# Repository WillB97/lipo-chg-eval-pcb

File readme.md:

# BQ25792/MP2759 LiPo Charger Evaluation Board

[GitHub Pages site](https://willb97.github.io/lipo-chg-eval-pcb/Browse/charger-compare-navigate.html).

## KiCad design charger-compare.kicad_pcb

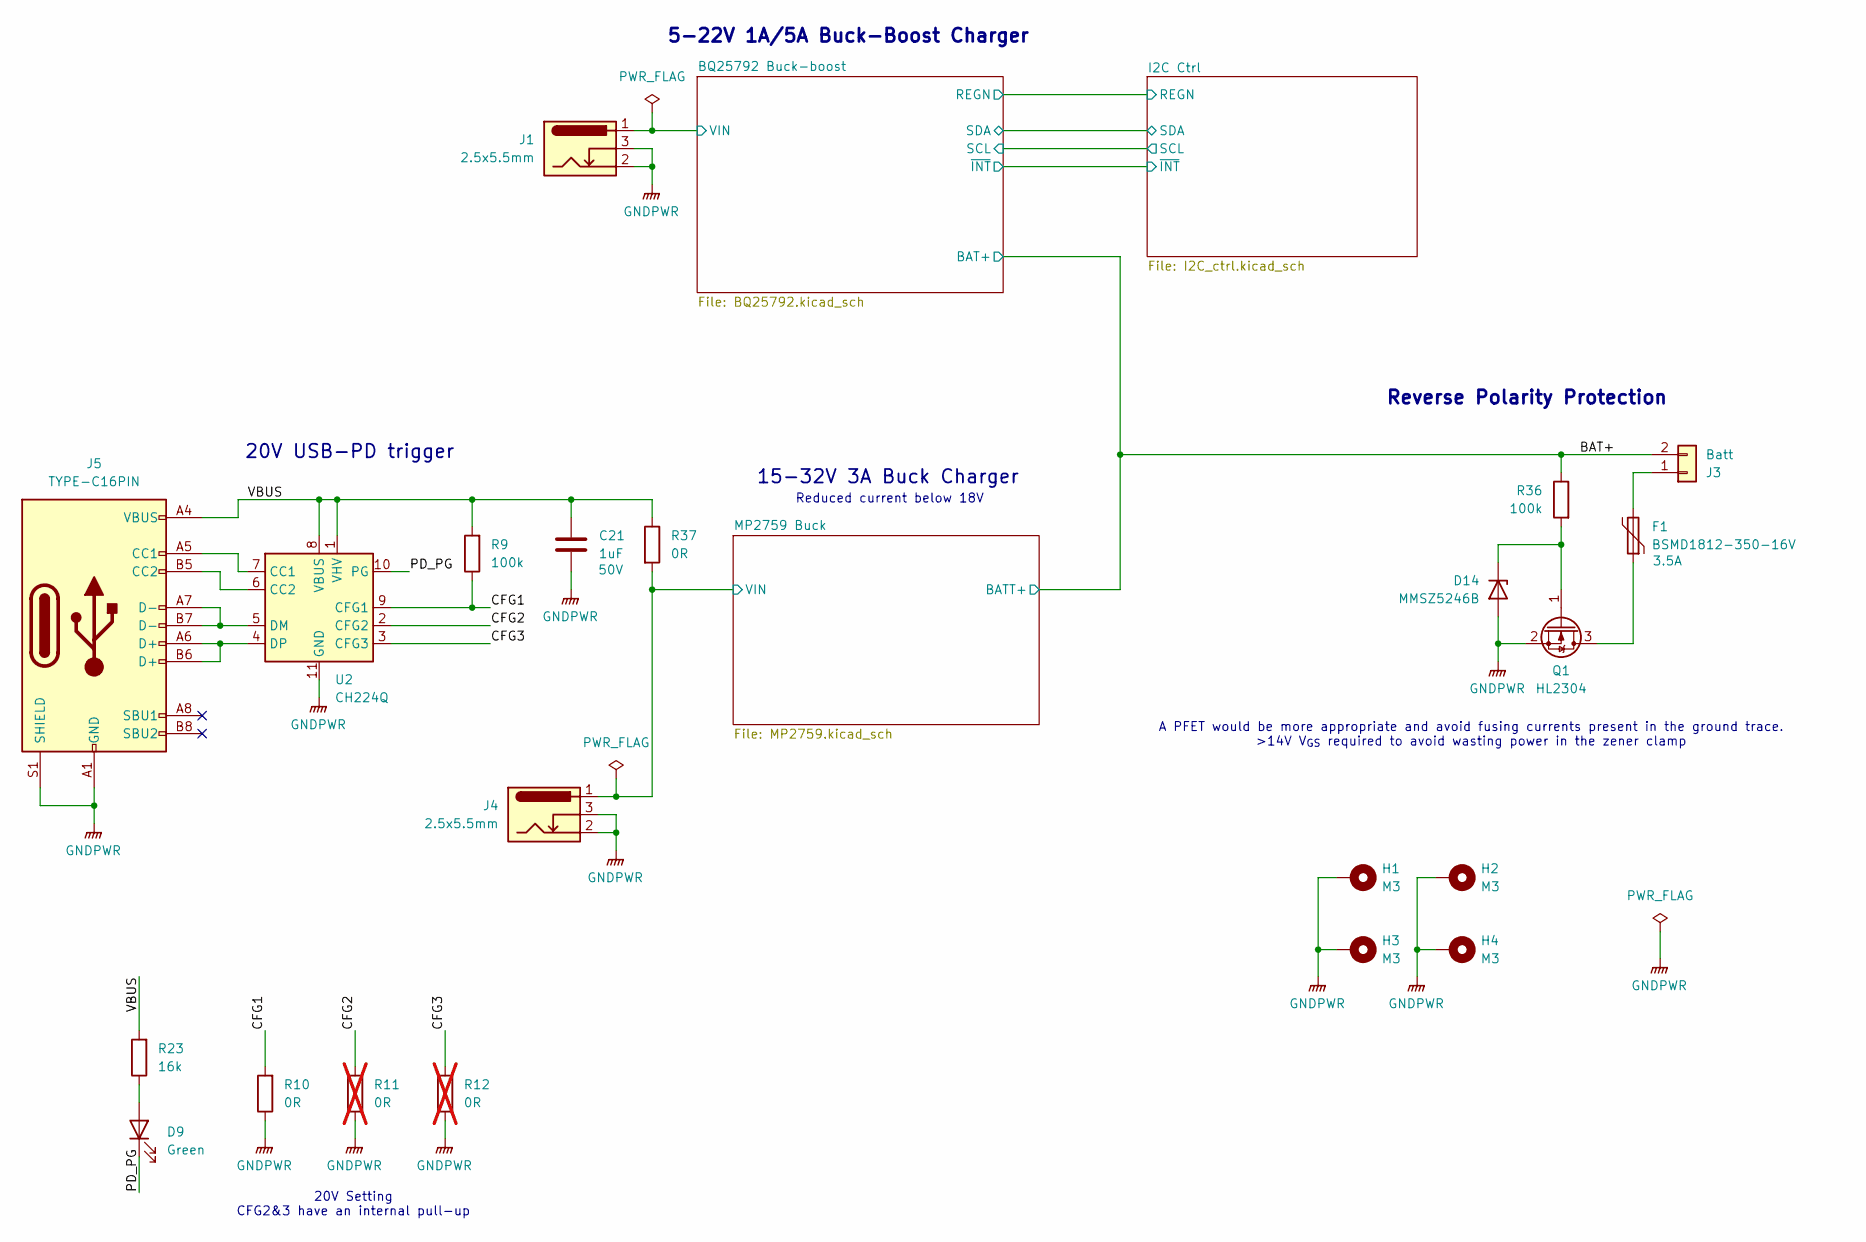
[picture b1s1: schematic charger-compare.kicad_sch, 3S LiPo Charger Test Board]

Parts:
C21: 1uF; C_0603_1608Metric; Voltage 50V; JLC C15849
D9: Green; LED_0805_2012Metric; JLC C2297
D14: MMSZ5246B; D_SOD-123; LCSC C19077429
F1: BSMD1812-350-16V; Fuse_1812_4532Metric_Pad1.30x3.40mm_HandSolder; Rating 3.5A; LCSC C5301865
H1, H2, H3, H4: M3; MountingHole_3.2mm_M3_Pad
J1, J4: 2.5x5.5mm; DC005-2.5; LCSC C7507454
J3: Batt; AMASS_XT60-M_1x02_P7.20mm_Vertical
J5: TYPE-C16PIN; USB_C_Receptacle_Palconn_UTC16-G; LCSC C393939
Q1: HL2304; SOT-23; LCSC C7420346
R9, R36: 100k; R_0402_1005Metric
R10: 0R; R_0603_1608Metric
R11, R12: 0R; R_0603_1608Metric; not fitted
R23: 16k; R_0402_1005Metric
R37: 0R; R_1206_3216Metric
U2: CH224Q; DFN-10_2x2mm_P0.4mm; LCSC C46061833

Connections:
/BAT+: J3.2, R36.1; also elsewhere on the board
/CFG1: R9.1, R10.2, U2.9 (CFG1)
/CFG2: R11.2, U2.2 (CFG2)
/CFG3: R12.2, U2.3 (CFG3)
/MP2759 Buck/VIN: J4.1, R37.2; also elsewhere on the board
/PD_PG: D9.1 (K), U2.10 (PG)
/VBUS: C21.1, J5.A4 (VBUS), J5.A9 (VBUS), J5.B4 (VBUS), J5.B9 (VBUS), R9.2, R23.2, R37.1, U2.1 (VHV), U2.8 (VBUS)
GNDPWR: C21.2, D14.2 (A), H1.1, H2.1, H3.1, H4.1, J1.2, J1.3, J4.2, J4.3, J5.A1 (GND), J5.A12 (GND), J5.B1 (GND), J5.B12 (GND), J5.S1 (SHIELD), Q1.2 (S), R10.1, R11.1, R12.1, U2.11 (GND); also elsewhere on the board
unnamed: D9.2 (A), R23.1
unnamed: D14.1 (K), Q1.1 (G), R36.2
unnamed: F1.2, J3.1
unnamed: J5.A5 (CC1), U2.7 (CC1)
unnamed: J5.B5 (CC2), U2.6 (CC2)
unnamed: F1.1, Q1.3 (D)
unnamed: J5.A7 (D-), J5.B7 (D-), U2.5 (DM)
unnamed: J5.A6 (D+), J5.B6 (D+), U2.4 (DP)
VBUS: J1.1; also elsewhere on the board

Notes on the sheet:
20V USB-PD trigger
Reverse Polarity Protection
5-22V 1A/5A Buck-Boost Charger
A PFET would be more appropriate and avoid fusing currents present in the ground trace. >14V V_{GS} required to avoid wasting power in the zener clamp
20V Setting CFG2&3 have an internal pull-up
Reduced current below 18V
15-32V 3A Buck Charger

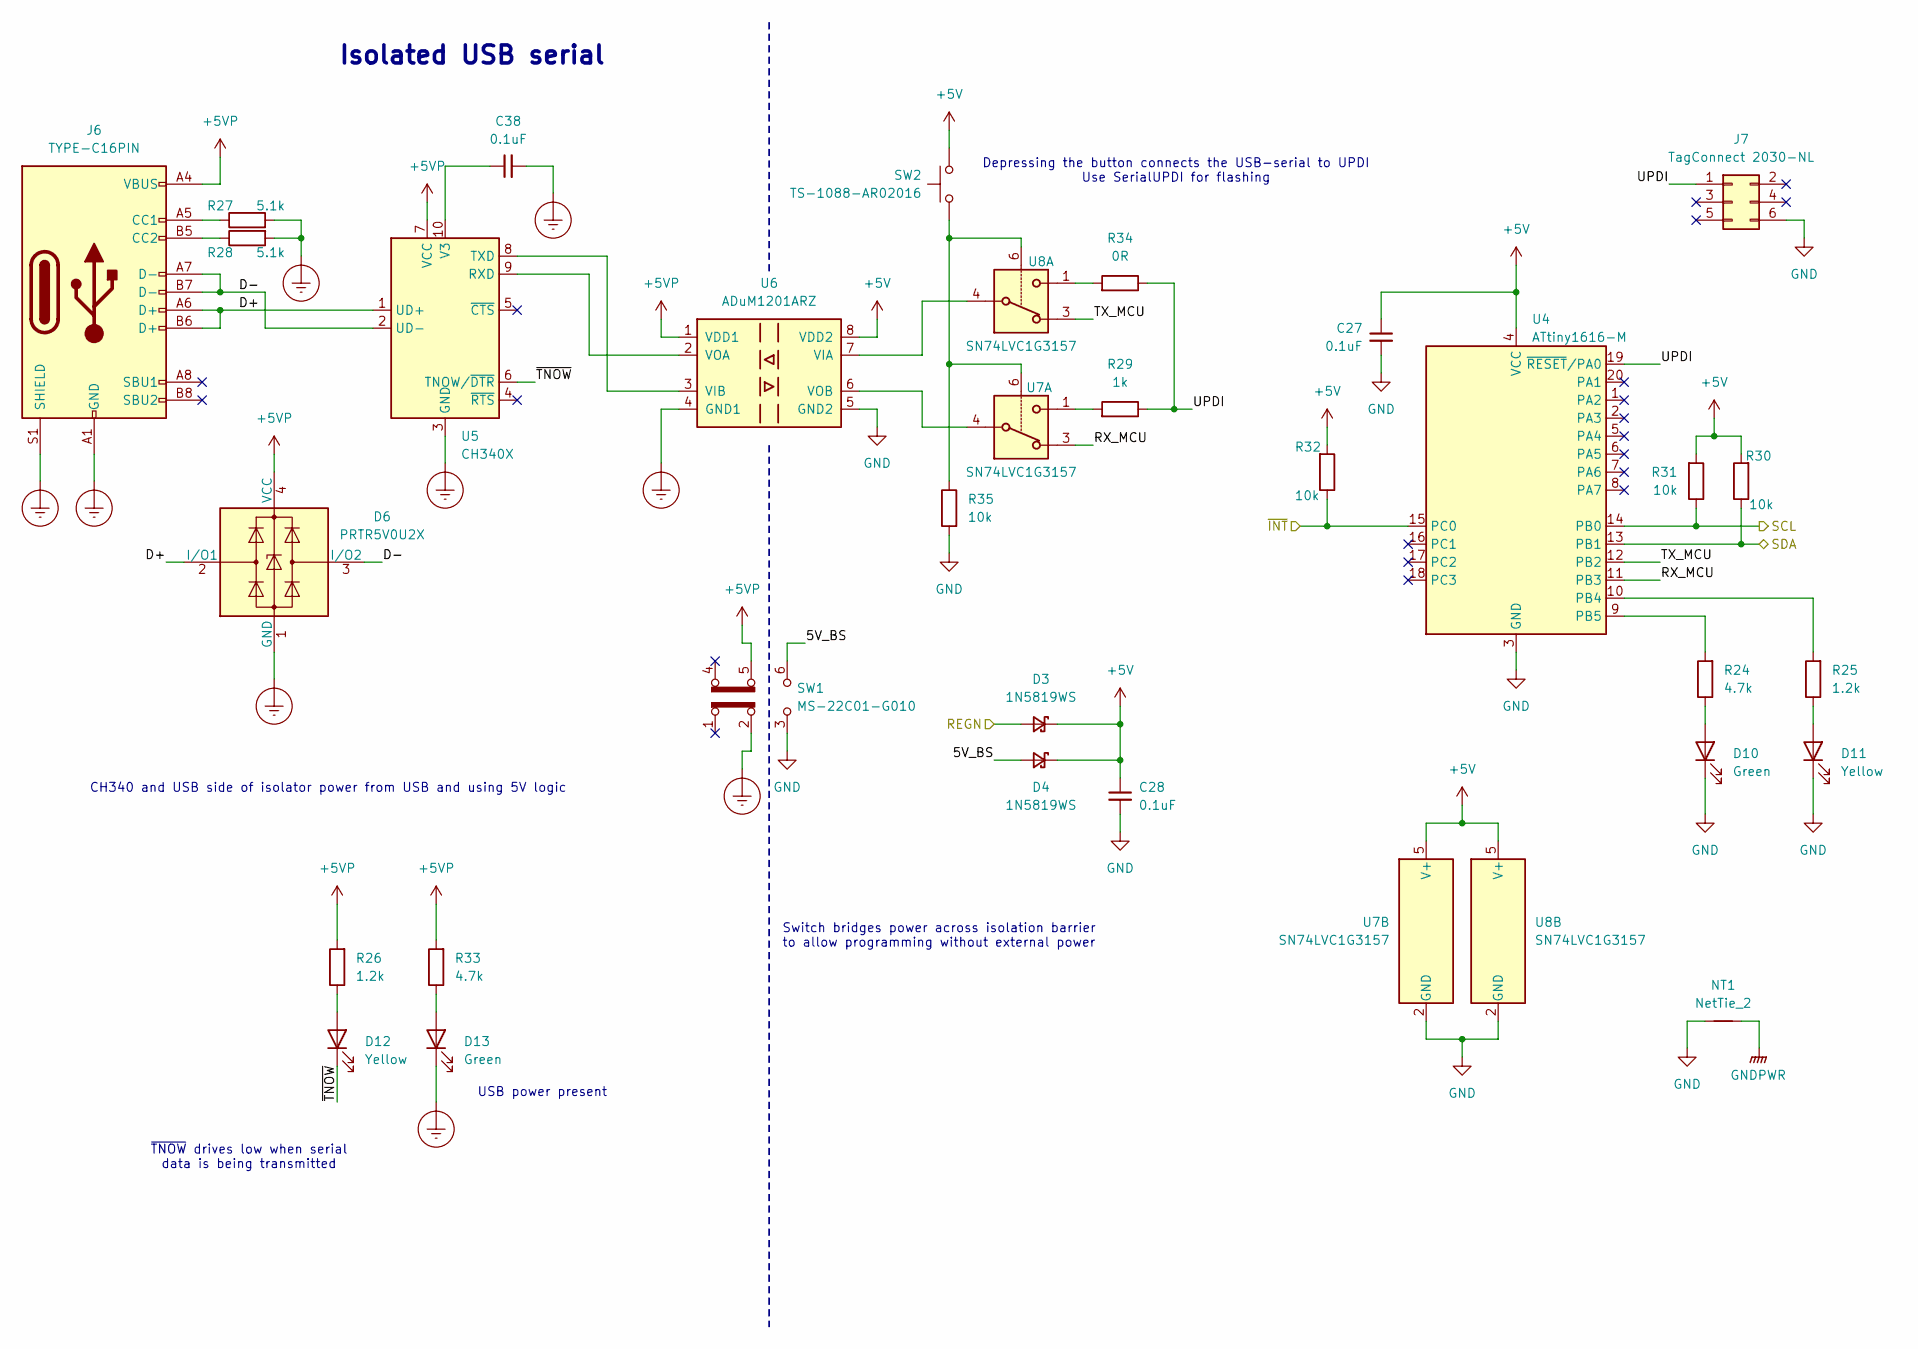
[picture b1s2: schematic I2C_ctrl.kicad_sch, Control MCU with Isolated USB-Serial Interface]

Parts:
C27, C28, C38: 0.1uF; C_0402_1005Metric; Voltage 10V; JLC C307331
D3, D4: 1N5819WS; D_SOD-323; JLC C191023
D6: PRTR5V0U2X; SOT-143; LCSC C5158049
D10, D13: Green; LED_0805_2012Metric; JLC C2297
D11, D12: Yellow; LED_0805_2012Metric; JLC C2296
J6: TYPE-C16PIN; USB_C_Receptacle_Palconn_UTC16-G; LCSC C393939
J7: TagConnect 2030-NL; Tag-Connect_TC2030-IDC-NL_2x03_P1.27mm_Vertical
NT1: NetTie_2; NetTie-2_SMD_Pad0.5mm
R24, R33: 4.7k; R_0402_1005Metric
R25, R26: 1.2k; R_0402_1005Metric
R27, R28: 5.1k; R_0402_1005Metric
R29: 1k; R_0402_1005Metric
R30, R31, R32, R35: 10k; R_0402_1005Metric
R34: 0R; R_0603_1608Metric
SW1: MS-22C01-G010; SW_DPDT_MS-22C01-G010
SW2: TS-1088-AR02016; SW_Push_SPST_JLC_Basic; JLC C720477
U4: ATtiny1616-M; VQFN-20-1EP_3x3mm_P0.4mm_EP1.7x1.7mm; LCSC C507118
U5: CH340X; MSOP-10_3x3mm_P0.5mm; LCSC C3035748
U6: ADuM1201ARZ; SOIC-8_3.9x4.9mm_P1.27mm; LCSC C9669
U7, U8: SN74LVC1G3157; SOT-363_SC-70-6; LCSC C36533656

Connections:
+5V: C27.1, C28.1, D3.1 (K), D4.1 (K), R30.2, R31.2, R32.2, SW2.2, U4.4 (VCC), U6.8 (VDD2), U7.5 (V+), U8.5 (V+)
+5VP: D6.4 (VCC), J6.A4 (VBUS), J6.A9 (VBUS), J6.B4 (VBUS), J6.B9 (VBUS), R26.2, R33.2, SW1.5 (B), U5.7 (VCC), U6.1 (VDD1)
/BQ25792 Buck-boost/REGN: D3.2 (A); also elsewhere on the board
/BQ25792 Buck-boost/SCL: R31.1, U4.14 (PB0); also elsewhere on the board
/BQ25792 Buck-boost/SDA: R30.1, U4.13 (PB1); also elsewhere on the board
/BQ25792 Buck-boost/~INT: R32.1, U4.15 (PC0); also elsewhere on the board
/I2C Ctrl/5V_BS: D4.2 (A), SW1.6 (C)
/I2C Ctrl/D+: D6.2 (I/O1), J6.A6 (D+), J6.B6 (D+), U5.1 (UD+)
/I2C Ctrl/D-: D6.3 (I/O2), J6.A7 (D-), J6.B7 (D-), U5.2 (UD-)
/I2C Ctrl/RX_MCU: U4.11 (PB3), U7.3
/I2C Ctrl/TX_MCU: U4.12 (PB2), U8.3
/I2C Ctrl/UPDI: J7.1, R29.1, R34.1, U4.19 (~RESET/PA0)
/I2C Ctrl/~TNOW: D12.1 (K), U5.6 (TNOW/~DTR)
Earth_Protective: C38.2, D6.1 (GND), D13.1 (K), J6.A1 (GND), J6.A12 (GND), J6.B1 (GND), J6.B12 (GND), J6.S1 (SHIELD), R27.2, R28.2, SW1.2 (B), U5.3 (GND), U6.4 (GND1)
GND: C27.2, C28.2, D10.1 (K), D11.1 (K), J7.6, NT1.1, R35.2, SW1.3 (C), U4.3 (GND), U4.21 (GND), U6.5 (GND2), U7.2 (GND), U8.2 (GND)
GNDPWR: NT1.2; also elsewhere on the board
unnamed: D10.2 (A), R24.1
unnamed: D11.2 (A), R25.1
unnamed: D12.2 (A), R26.1
unnamed: D13.2 (A), R33.1
unnamed: J6.A5 (CC1), R27.1
unnamed: J6.B5 (CC2), R28.1
unnamed: R29.2, U7.1
unnamed: R34.2, U8.1
unnamed: R35.1, SW2.1, U7.6, U8.6
unnamed: R25.2, U4.10 (PB4)
unnamed: R24.2, U4.9 (PB5)
unnamed: U5.9 (RXD), U6.2 (VOA)
unnamed: U5.8 (TXD), U6.3 (VIB)
unnamed: C38.1, U5.10 (V3)
unnamed: U6.7 (VIA), U8.4
unnamed: U6.6 (VOB), U7.4

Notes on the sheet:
~{TNOW} drives low when serial data is being transmitted
Depressing the button connects the USB-serial to UPDI Use SerialUPDI for flashing
Switch bridges power across isolation barrier to allow programming without external power
USB power present
Isolated USB serial
CH340 and USB side of isolator power from USB and using 5V logic

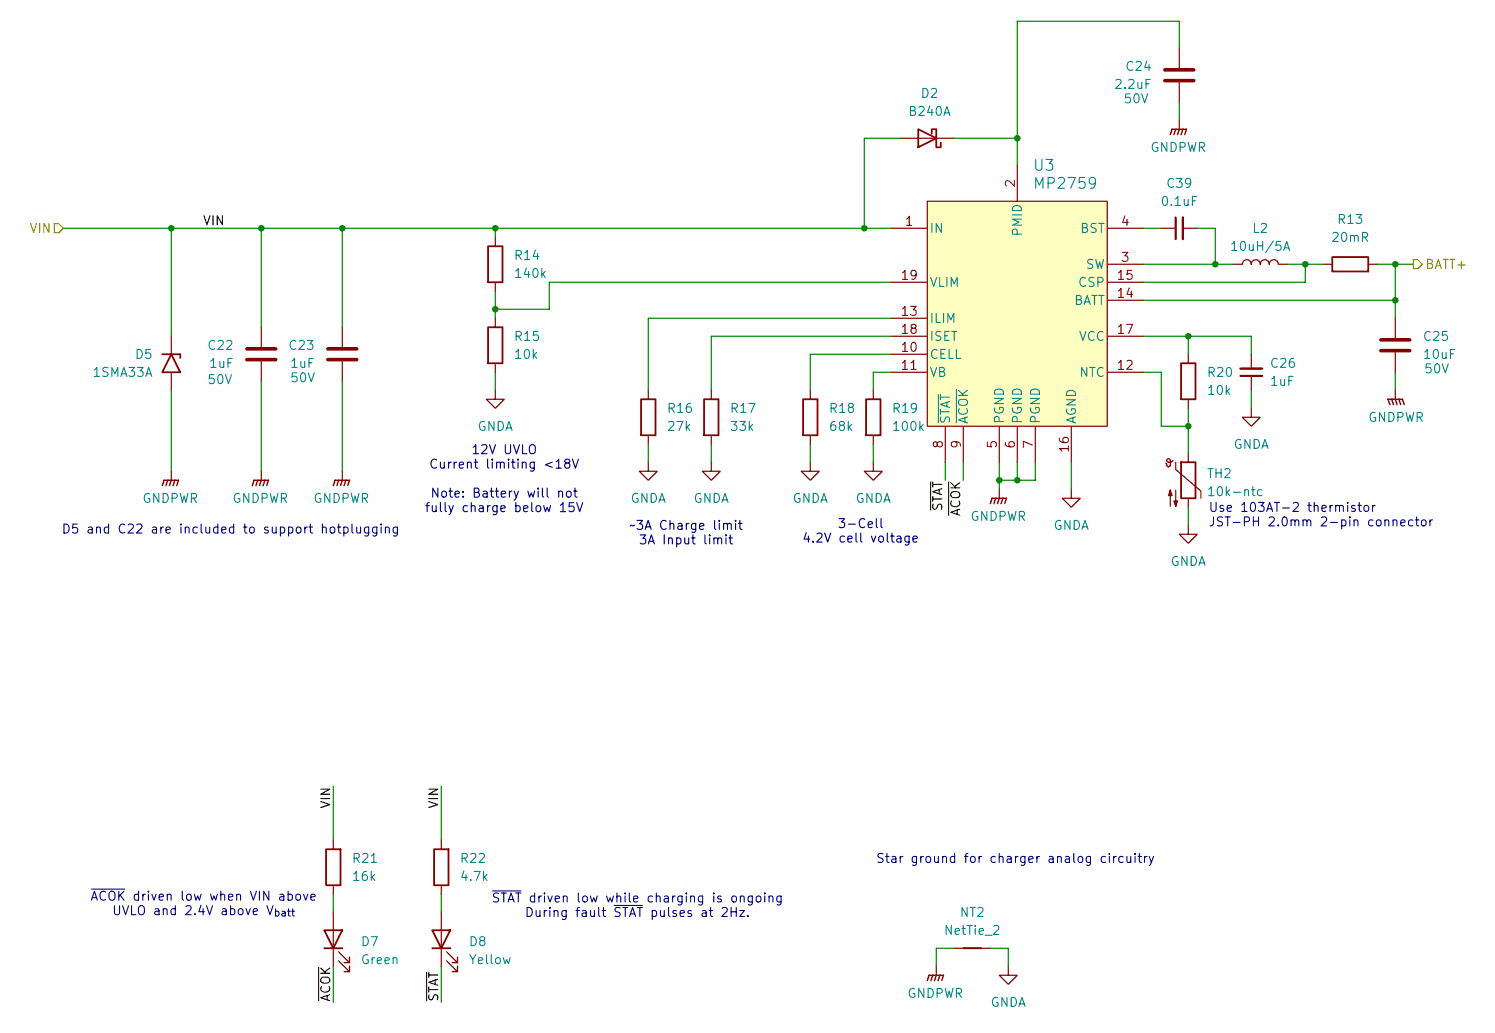
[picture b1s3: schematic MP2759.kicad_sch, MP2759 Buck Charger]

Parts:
C22, C23: 1uF; C_0603_1608Metric; Voltage 50V; JLC C15849
C24: 2.2uF; C_0805_2012Metric; Voltage 50V; JLC C377773
C25: 10uF; C_0805_2012Metric; Voltage 50V; JLC C440198
C26: 1uF; C_0603_1608Metric; Voltage 10V; JLC C15849
C39: 0.1uF; C_0402_1005Metric; Voltage 10V; JLC C307331
D2: B240A; D_SMA; LCSC C39358
D5: 1SMA33A; D_SMA; LCSC C1975650
D7: Green; LED_0805_2012Metric; JLC C2297
D8: Yellow; LED_0805_2012Metric; JLC C2296
L2: 10uH/5A; L_Bourns_SRP7028A_7.3x6.6mm; LCSC C32712974
NT2: NetTie_2; NetTie-2_SMD_Pad0.5mm
R13: 20mR; R_1206_3216Metric; LCSC C393094
R14: 140k; R_0402_1005Metric; LCSC C2998127
R15, R20: 10k; R_0402_1005Metric
R16: 27k; R_0603_1608Metric
R17: 33k; R_0402_1005Metric
R18: 68k; R_0603_1608Metric
R19: 100k; R_0402_1005Metric
R21: 16k; R_0402_1005Metric
R22: 4.7k; R_0402_1005Metric
TH2: 10k-ntc; JST_PH_B2B-PH-K_1x02_P2.00mm_Vertical
U3: MP2759; QFN-19_MP2759_MNP; LCSC C3682359

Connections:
/BAT+: C25.1, R13.2, U3.14 (BATT); also elsewhere on the board
/MP2759 Buck/VIN: C22.1, C23.1, D2.2 (A), D5.1 (A1), R14.1, R21.2, R22.2, U3.1 (IN); also elsewhere on the board
/MP2759 Buck/~ACOK: D7.1 (K), U3.9 (~ACOK)
/MP2759 Buck/~STAT: D8.1 (K), U3.8 (~STAT)
GNDA: C26.1, NT2.2, R15.2, R16.2, R17.2, R18.2, R19.2, TH2.2, U3.16 (AGND)
GNDPWR: C22.2, C23.2, C24.2, C25.2, D5.2 (A2), NT2.1, U3.5 (PGND), U3.6 (PGND), U3.7 (PGND); also elsewhere on the board
unnamed: C24.1, D2.1 (K), U3.2 (PMID)
unnamed: D7.2 (A), R21.1
unnamed: D8.2 (A), R22.1
unnamed: C39.1, U3.4 (BST)
unnamed: R18.1, U3.10 (CELL)
unnamed: L2.2, R13.1, U3.15 (CSP)
unnamed: R16.1, U3.13 (ILIM)
unnamed: R17.1, U3.18 (ISET)
unnamed: R20.2, TH2.1, U3.12 (NTC)
unnamed: C39.2, L2.1, U3.3 (SW)
unnamed: R19.1, U3.11 (VB)
unnamed: C26.2, R20.1, U3.17 (VCC)
unnamed: R14.2, R15.1, U3.19 (VLIM)

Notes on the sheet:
~3A Charge limit 3A Input limit
3-Cell 4.2V cell voltage
Use 103AT-2 thermistor JST-PH 2.0mm 2-pin connector
D5 and C22 are included to support hotplugging
~{STAT} driven low while charging is ongoing During fault ~{STAT} pulses at 2Hz.
~{ACOK} driven low when VIN above UVLO and 2.4V above V_{batt}
12V UVLO Current limiting <18V Note: Battery will not fully charge below 15V
Star ground for charger analog circuitry

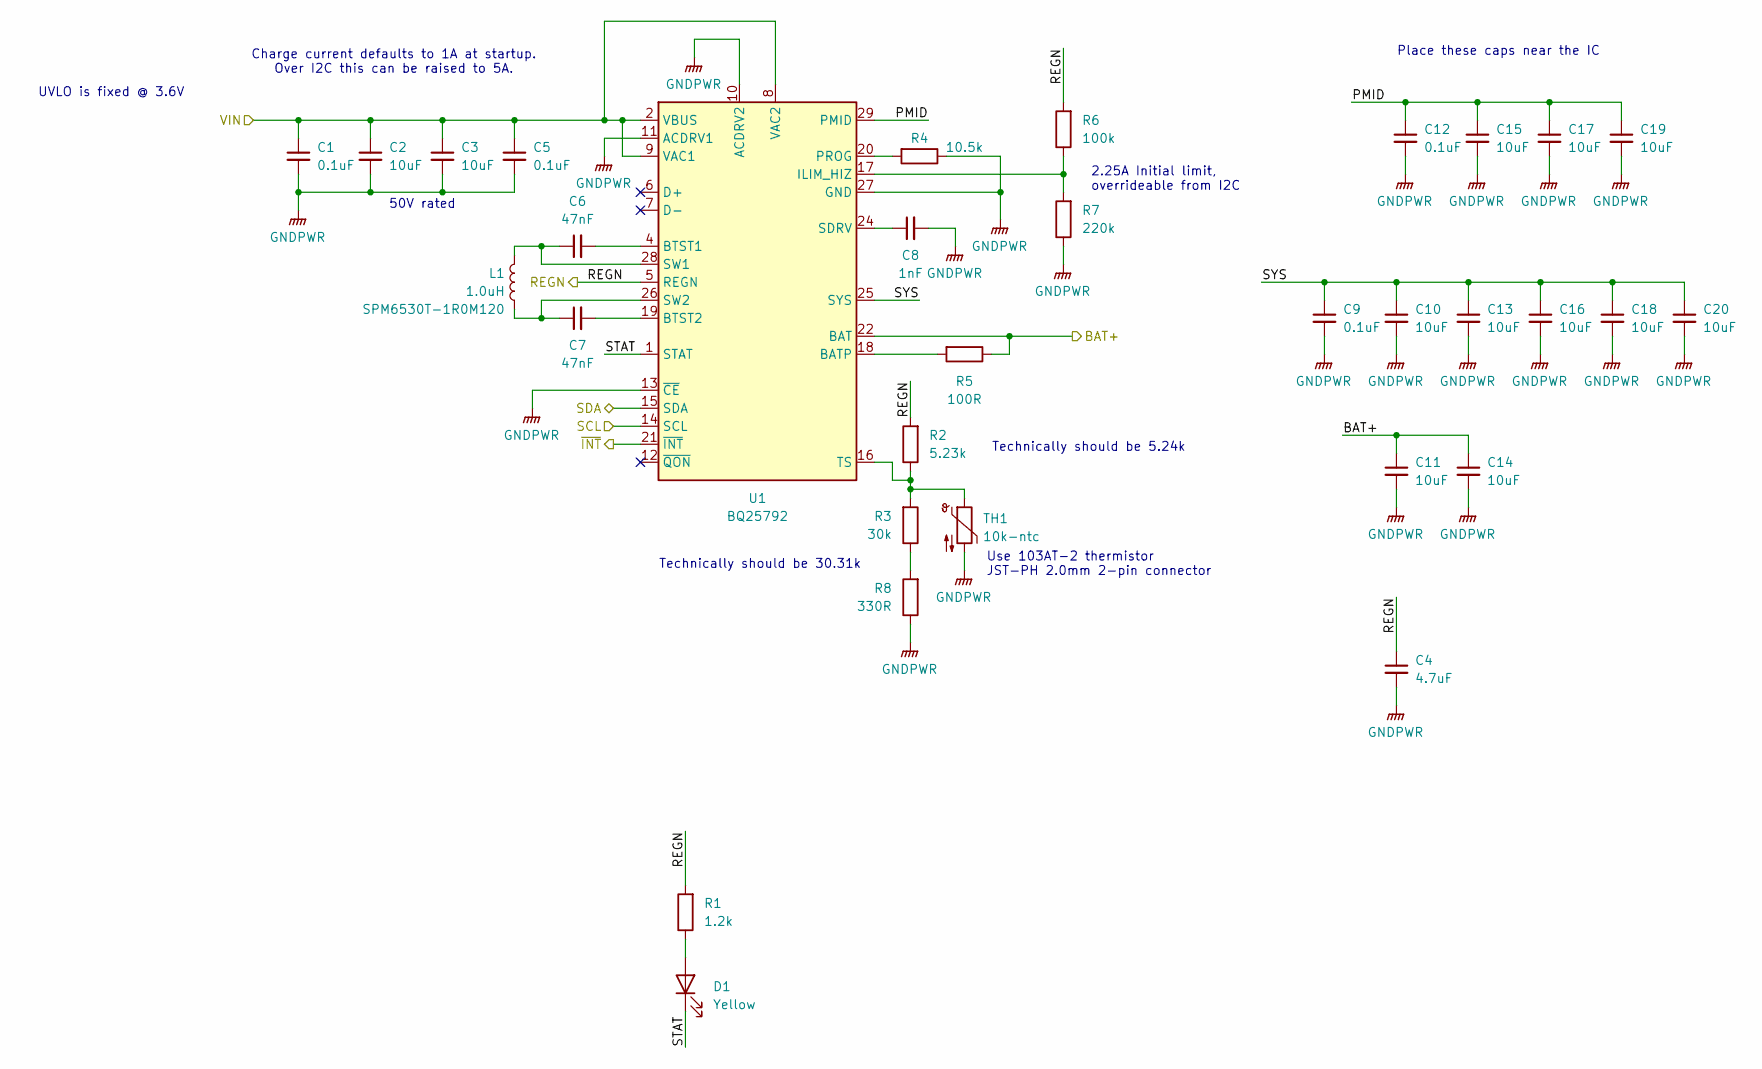
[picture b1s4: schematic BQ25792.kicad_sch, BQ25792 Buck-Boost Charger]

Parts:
C1, C5, C9, C12: 0.1uF; C_0402_1005Metric; Voltage 50V; JLC C307331
C2, C3: 10uF; C_0805_2012Metric; Voltage 50V; JLC C440198
C4: 4.7uF; C_0402_1005Metric; Voltage 6.3V; JLC C23733
C6, C7: 47nF; C_0402_1005Metric; Voltage 50V; LCSC C307339
C8: 1nF; C_0402_1005Metric; Voltage 50V; JLC C1523
C10, C11, C13, C14, C15, C16, C17, C18, C19, C20: 10uF; C_0805_2012Metric; Voltage 25V; JLC C15850
D1: Yellow; LED_0805_2012Metric; JLC C2296
L1: 1.0uH; TDK-SPM6530T; LCSC C87572
R1: 1.2k; R_0402_1005Metric
R2: 5.23k; R_0603_1608Metric; LCSC C5140106
R3: 30k; R_0603_1608Metric
R4: 10.5k; R_0603_1608Metric; LCSC C100712
R5: 100R; R_0402_1005Metric
R6: 100k; R_0402_1005Metric
R7: 220k; R_0603_1608Metric
R8: 330R; R_0402_1005Metric
TH1: 10k-ntc; JST_PH_B2B-PH-K_1x02_P2.00mm_Vertical
U1: BQ25792; VQFN29-HR; LCSC C2862876

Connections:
/BAT+: C11.1, C14.1, R5.1, U1.22 (BAT), U1.23 (BAT); also elsewhere on the board
/BQ25792 Buck-boost/PMID: C12.1, C15.1, C17.1, C19.1, U1.29 (PMID)
/BQ25792 Buck-boost/REGN: C4.1, R1.2, R2.2, R6.2, U1.5 (REGN); also elsewhere on the board
/BQ25792 Buck-boost/SCL: U1.14 (SCL); also elsewhere on the board
/BQ25792 Buck-boost/SDA: U1.15 (SDA); also elsewhere on the board
/BQ25792 Buck-boost/STAT: D1.1 (K), U1.1 (STAT)
/BQ25792 Buck-boost/SYS: C9.1, C10.1, C13.1, C16.1, C18.1, C20.1, U1.25 (SYS)
/BQ25792 Buck-boost/~INT: U1.21 (~INT); also elsewhere on the board
GNDPWR: C1.2, C2.2, C3.2, C4.2, C5.2, C8.2, C9.2, C10.2, C11.2, C12.2, C13.2, C14.2, C15.2, C16.2, C17.2, C18.2, C19.2, C20.2, R4.1, R7.1, R8.1, TH1.2, U1.10 (ACDRV2), U1.11 (ACDRV1), U1.13 (~CE), U1.27 (GND); also elsewhere on the board
unnamed: D1.2 (A), R1.1
unnamed: R3.1, R8.2
unnamed: R5.2, U1.18 (BATP)
unnamed: C6.2, U1.4 (BTST1)
unnamed: C7.2, U1.19 (BTST2)
unnamed: R6.1, R7.2, U1.17 (ILIM_HIZ)
unnamed: R4.2, U1.20 (PROG)
unnamed: C8.1, U1.24 (SDRV)
unnamed: C6.1, L1.1, U1.28 (SW1)
unnamed: C7.1, L1.2, U1.26 (SW2)
unnamed: R2.1, R3.2, TH1.1, U1.16 (TS)
VBUS: C1.1, C2.1, C3.1, C5.1, U1.2 (VBUS), U1.3 (VBUS), U1.8 (VAC2), U1.9 (VAC1); also elsewhere on the board

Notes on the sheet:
UVLO is fixed @ 3.6V
2.25A Initial limit, overrideable from I2C
Place these caps near the IC
Use 103AT-2 thermistor JST-PH 2.0mm 2-pin connector
Technically should be 30.31k
50V rated
Charge current defaults to 1A at startup. Over I2C this can be raised to 5A.
Technically should be 5.24k

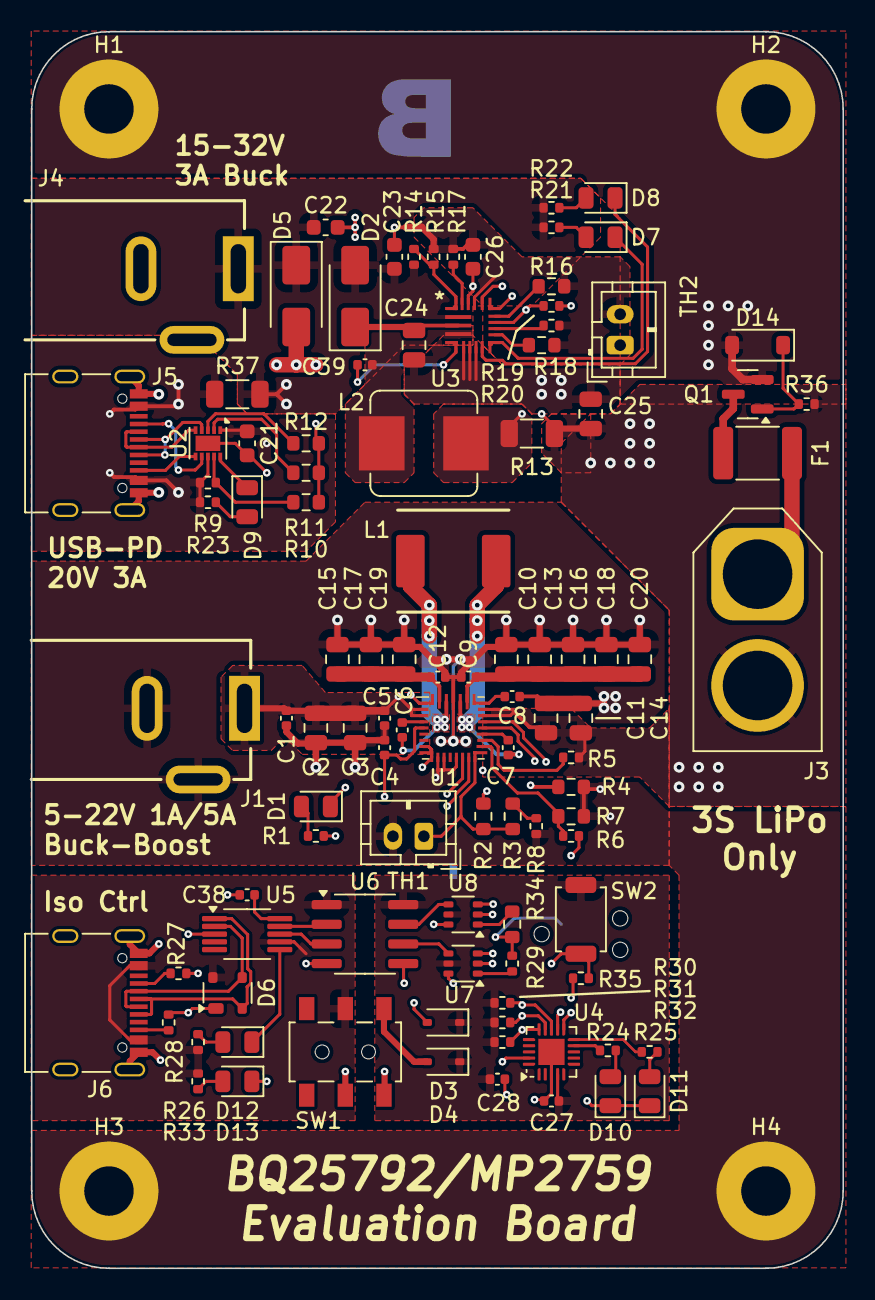
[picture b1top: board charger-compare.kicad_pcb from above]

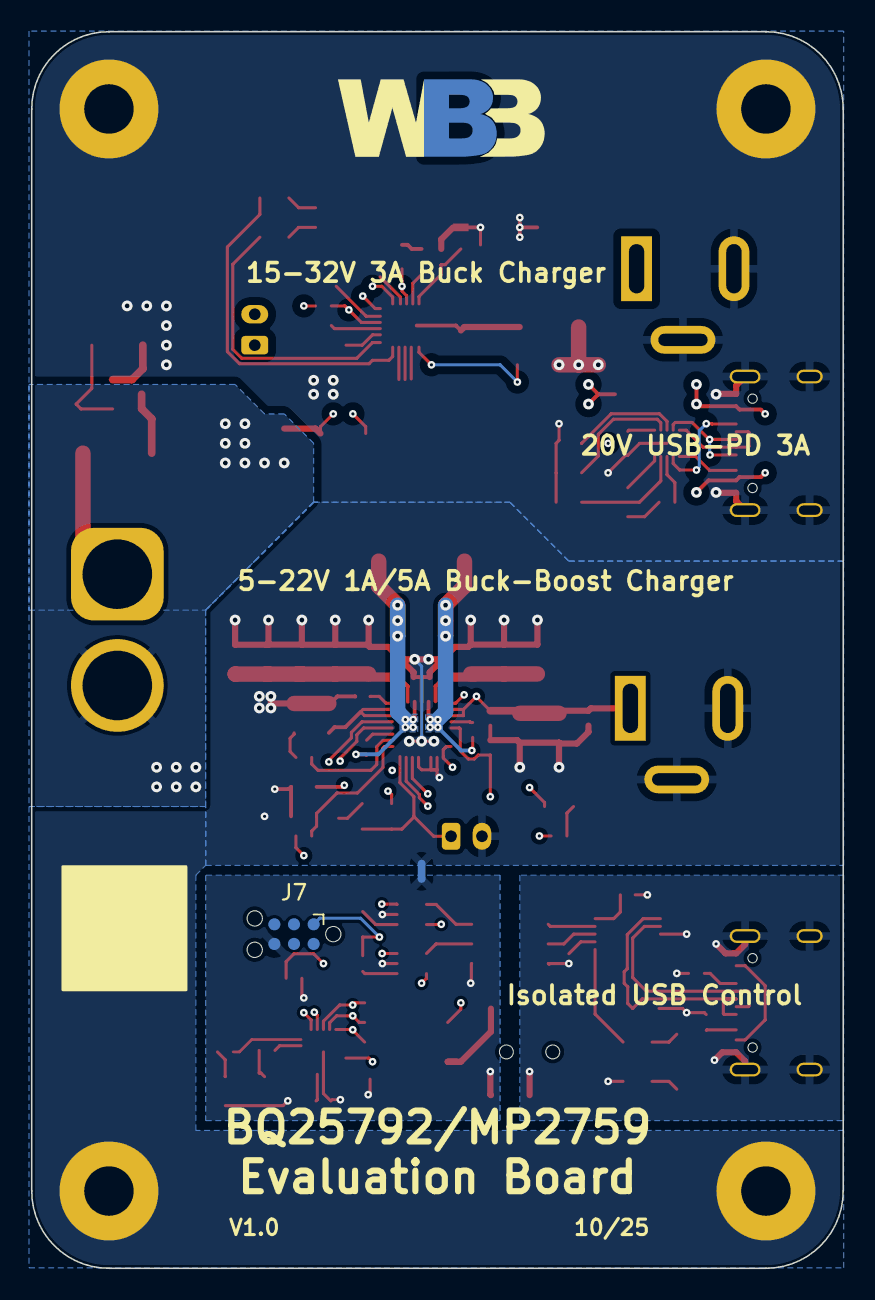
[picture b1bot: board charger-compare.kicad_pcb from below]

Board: 4 copper layers, 52.5 x 80.0 mm, 110 parts (3 on the bottom side), 78 nets.

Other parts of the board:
LBL1: WBB

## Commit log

2025-10-05 Initial design
2025-10-05 Add some CI
2025-10-05 More fixes
2025-10-06 Enable github pages
2025-10-06 Fix reference
2025-10-06 Try older KiBot Add readme
2025-10-06 Put readme in correct location
2025-10-07 Set LED resistors
2025-10-09 Switch to JST-PH connectors Add Sheet titles
2025-10-11 Use custom kibot config
2025-10-11 Try generating kibot configs
2025-10-11 Update gitignore
2025-10-15 Action review feedback
2025-10-16 Add JLC QR code location
2025-10-16 Omit tagconnect for BOM
2025-10-16 Add V1.0 date
